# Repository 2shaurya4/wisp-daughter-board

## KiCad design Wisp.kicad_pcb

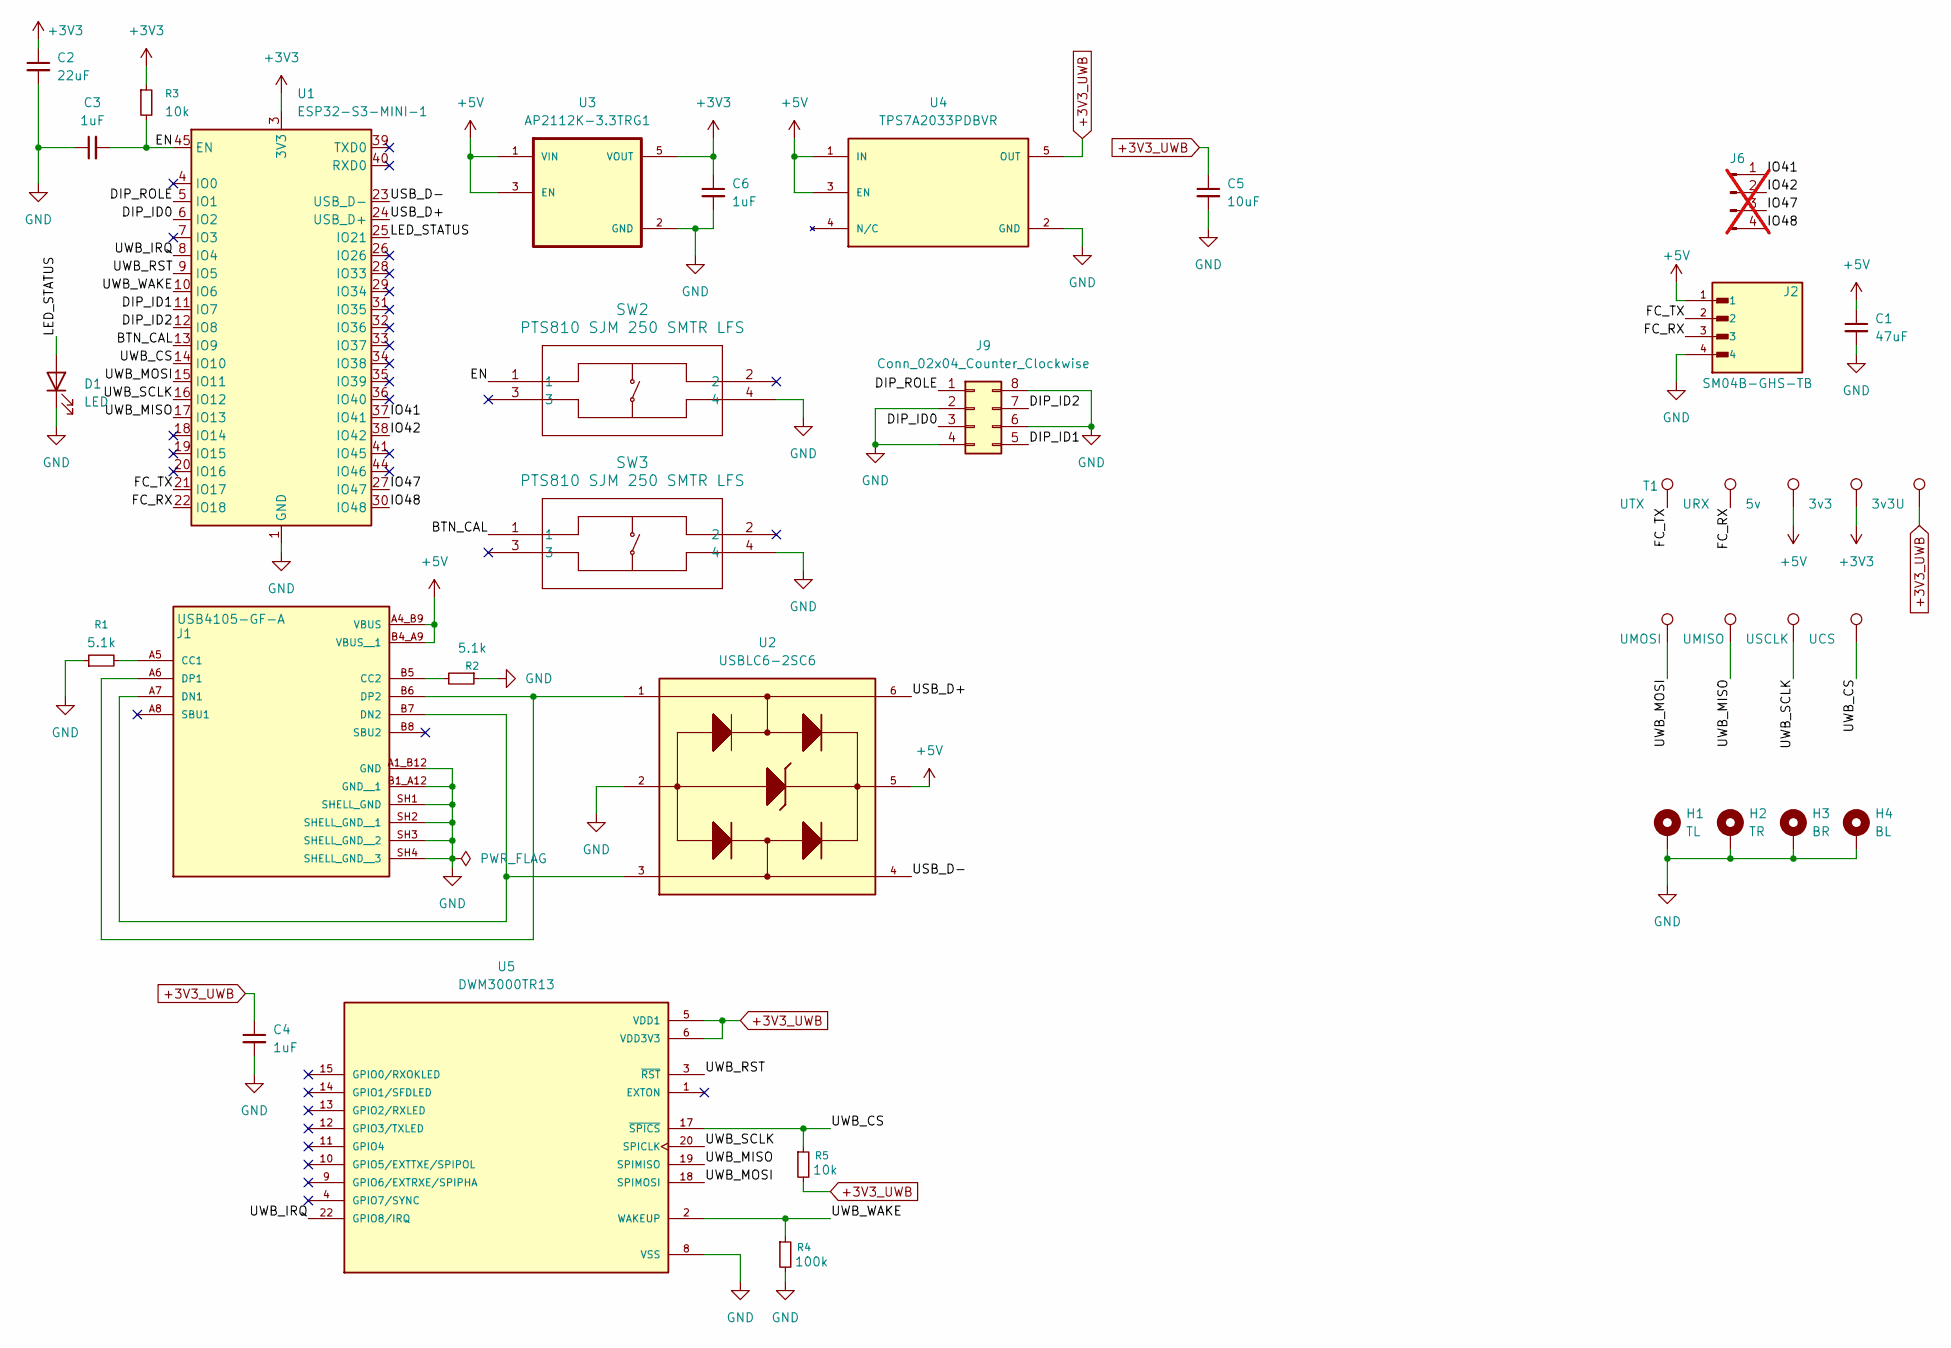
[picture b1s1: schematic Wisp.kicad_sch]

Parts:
C1: 47uF; C_0603_1608Metric
C2: 22uF; C_0603_1608Metric
C3, C4, C6: 1uF; C_0603_1608Metric
C5: 10uF; C_0603_1608Metric
D1: LED; LED_0603_1608Metric
H1: TL; MountingHole_3.2mm_M3_Pad_Via
H2: TR; MountingHole_3.2mm_M3_Pad_Via
H3: BR; MountingHole_3.2mm_M3_Pad_Via
H4: BL; MountingHole_3.2mm_M3_Pad_Via
J1: USB4105-GF-A; GCT_USB4105-GF-A; PARTREV B4
J2: SM04B-GHS-TB; JST_SM04B-GHS-TB
J6: Conn_01x04_Pin; PinHeader_1x04_P2.54mm_Vertical_SMD_Pin1Right; not fitted
J9: Conn_02x04_Counter_Clockwise; PinHeader_2x04_P2.00mm_Vertical
R1, R2: 5.1k; R_0603_1608Metric
R3, R5: 10k; R_0603_1608Metric
R4: 100k; R_0603_1608Metric
SW2, SW3: PTS810 SJM 250 SMTR LFS; PTS810_CNK
T1: UTX; TestPoint_Pad_1.0x1.0mm
TP2: URX; TestPoint_Pad_1.0x1.0mm
TP3: 5v; TestPoint_Pad_1.0x1.0mm
TP4: 3v3; TestPoint_Pad_1.0x1.0mm
TP5: 3v3U; TestPoint_Pad_1.0x1.0mm
TP6: UMOSI; TestPoint_Pad_1.0x1.0mm
TP7: UMISO; TestPoint_Pad_1.0x1.0mm
TP8: USCLK; TestPoint_Pad_1.0x1.0mm
TP9: UCS; TestPoint_Pad_1.0x1.0mm
U1: ESP32-S3-MINI-1; ESP32-S2-MINI-1
U2: USBLC6-2SC6; SOT95P280X145-6N
U3: AP2112K-3.3TRG1; SOT95P285X140-5N; PARTREV 2-2; DigiKey_Part_Number AP2112K-3.3TRG1DICT-ND
U4: TPS7A2033PDBVR; SOT95P280X145-5N; PARTREV H
U5: DWM3000TR13; XCVR_DWM3000TR13; PARTREV B

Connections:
+3V3: C2.1, C6.1, R3.1, TP4.1 (1_1), U1.3 (3V3), U3.5 (VOUT)
+3V3_UWB: C4.1, C5.1, R5.2, TP5.1 (1_1), U4.5 (OUT), U5.5 (VDD1), U5.6 (VDD3V3), U5.7 (VDD3V3)
+5V: C1.1, J1.A4_B9 (VBUS), J1.B4_A9 (VBUS__1), J2.1, TP3.1 (1_1), U2.5, U3.1 (VIN), U3.3 (EN), U4.1 (IN), U4.3 (EN)
/BTN_CAL: SW3.1, U1.13 (IO9)
/DIP_ID0: J9.3, U1.6 (IO2)
/DIP_ID1: J9.5, U1.11 (IO7)
/DIP_ID2: J9.7, U1.12 (IO8)
/DIP_ROLE: J9.1, U1.5 (IO1)
/EN: C3.2, R3.2, SW2.1, U1.45 (EN)
/FC_RX: J2.3, TP2.1 (1_1), U1.22 (IO18)
/FC_TX: J2.2, T1.1, U1.21 (IO17); also elsewhere on the board
/IO41: J6.1, U1.37 (IO41)
/IO42: J6.2, U1.38 (IO42)
/IO47: J6.3, U1.27 (IO47)
/IO48: J6.4, U1.30 (IO48)
/LED_STATUS: D1.2 (A), U1.25 (IO21)
/USB_D+: U1.24 (USB_D+), U2.6
/USB_D-: U1.23 (USB_D-), U2.4
/UWB_CS: R5.1, TP9.1 (1_1), U1.14 (IO10), U5.17 (~SPICS)
/UWB_IRQ: U1.8 (IO4), U5.22 (GPIO8/IRQ)
/UWB_MISO: TP7.1 (1_1), U1.17 (IO13), U5.19 (SPIMISO)
/UWB_MOSI: TP6.1 (1_1), U1.15 (IO11), U5.18 (SPIMOSI)
/UWB_RST: U1.9 (IO5), U5.3 (~RST)
/UWB_SCLK: TP8.1 (1_1), U1.16 (IO12), U5.20 (SPICLK)
/UWB_WAKE: R4.1, U1.10 (IO6), U5.2 (WAKEUP)
GND: C1.2, C2.2, C3.1, C4.2, C5.2, C6.2, D1.1 (K), H1.MP, H2.MP, H3.MP, H4.MP, J1.A1_B12 (GND), J1.B1_A12 (GND__1), J1.SH1 (SHELL_GND), J1.SH2 (SHELL_GND__1), J1.SH3 (SHELL_GND__2), J1.SH4 (SHELL_GND__3), J2.4, J9.2, J9.4, J9.6, J9.8, R1.1, R2.1, R4.2, SW2.4, SW3.4, U1.1 (GND), U1.2 (GND), U1.42 (GND), U1.43 (GND), U1.46 (GND), U1.47 (GND), U1.48 (GND), U1.49 (GND), U1.50 (GND), U1.51 (GND), U1.52 (GND), U1.53 (GND), U1.54 (GND), U1.55 (GND), U1.56 (GND), U1.57 (GND), U1.58 (GND), U1.59 (GND), U1.60 (GND), U1.61 (GND), U1.62 (GND), U1.63 (GND), U1.64 (GND), U1.65 (GND), U2.2, U3.2 (GND), U4.2 (GND), U5.8 (VSS), U5.16 (VSS), U5.21 (VSS), U5.23 (VSS), U5.24 (VSS)
unnamed: J1.A5 (CC1), R1.2
unnamed: J1.B5 (CC2), R2.2
unnamed: J1.A7 (DN1), J1.B7 (DN2), U2.3
unnamed: J1.A6 (DP1), J1.B6 (DP2), U2.1

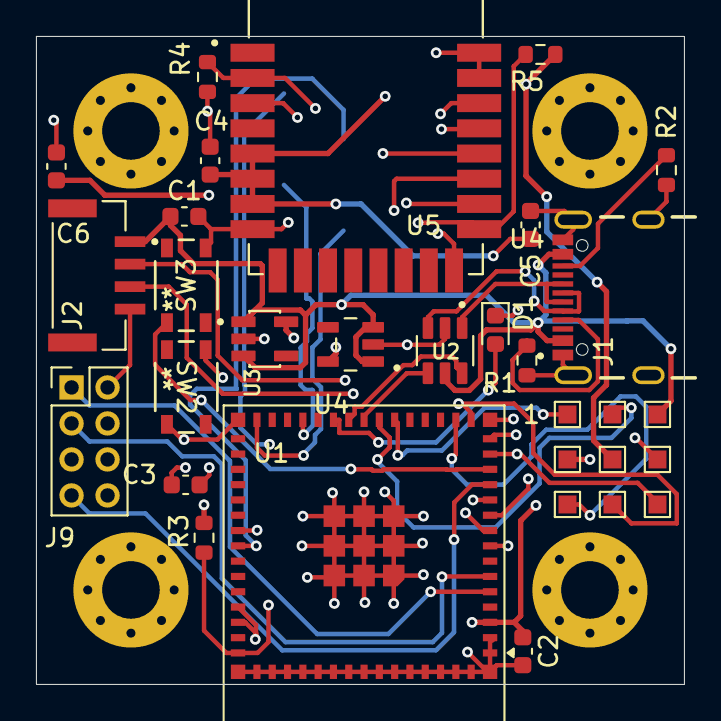
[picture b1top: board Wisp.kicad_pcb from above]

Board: 4 copper layers, 36.0 x 36.0 mm, 36 parts (1 on the bottom side), 30 nets.

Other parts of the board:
1: UTX; TestPoint_Pad_1.0x1.0mm

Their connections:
/FC_TX: 1.1 (1_1); also elsewhere on the board

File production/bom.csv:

Designator,Footprint,Quantity,Value,LCSC Part #
1,TestPoint_Pad_1.0x1.0mm,1,UTX,
C1,0603,1,47uF,
C2,0603,1,22uF,
"C3, C4, C6",0603,3,1uF,
C5,0603,1,10uF,
D1,0603,1,LED,
J1,GCT_USB4105-GF-A,1,USB4105-GF-A,
J2,JST_SM04B-GHS-TB,1,SM04B-GHS-TB,
J6,PinHeader_1x04_P2.54mm_Vertical_SMD_Pin1Right,1,Conn_01x04_Pin,
J9,PinHeader_2x04_P2.00mm_Vertical,1,Conn_02x04_Counter_Clockwise,
"R1, R2",0603,2,5.1k,
"R3, R5",0603,2,10k,
R4,0603,1,100k,
"SW2, SW3",PTS810_CNK,2,PTS810 SJM 250 SMTR LFS,
TP2,TestPoint_Pad_1.0x1.0mm,1,URX,
TP3,TestPoint_Pad_1.0x1.0mm,1,5v,
TP4,TestPoint_Pad_1.0x1.0mm,1,3v3,
TP5,TestPoint_Pad_1.0x1.0mm,1,3v3U,
TP6,TestPoint_Pad_1.0x1.0mm,1,UMOSI,
TP7,TestPoint_Pad_1.0x1.0mm,1,UMISO,
TP8,TestPoint_Pad_1.0x1.0mm,1,USCLK,
TP9,TestPoint_Pad_1.0x1.0mm,1,UCS,
U1,ESP32-S2-MINI-1,1,ESP32-S3-MINI-1,
U2,SOT95P280X145-6N,1,USBLC6-2SC6,
U3,SOT95P285X140-5N,1,AP2112K-3.3TRG1,
U4,SOT95P280X145-5N,1,TPS7A2033PDBVR,
U5,XCVR_DWM3000TR13,1,DWM3000TR13,
